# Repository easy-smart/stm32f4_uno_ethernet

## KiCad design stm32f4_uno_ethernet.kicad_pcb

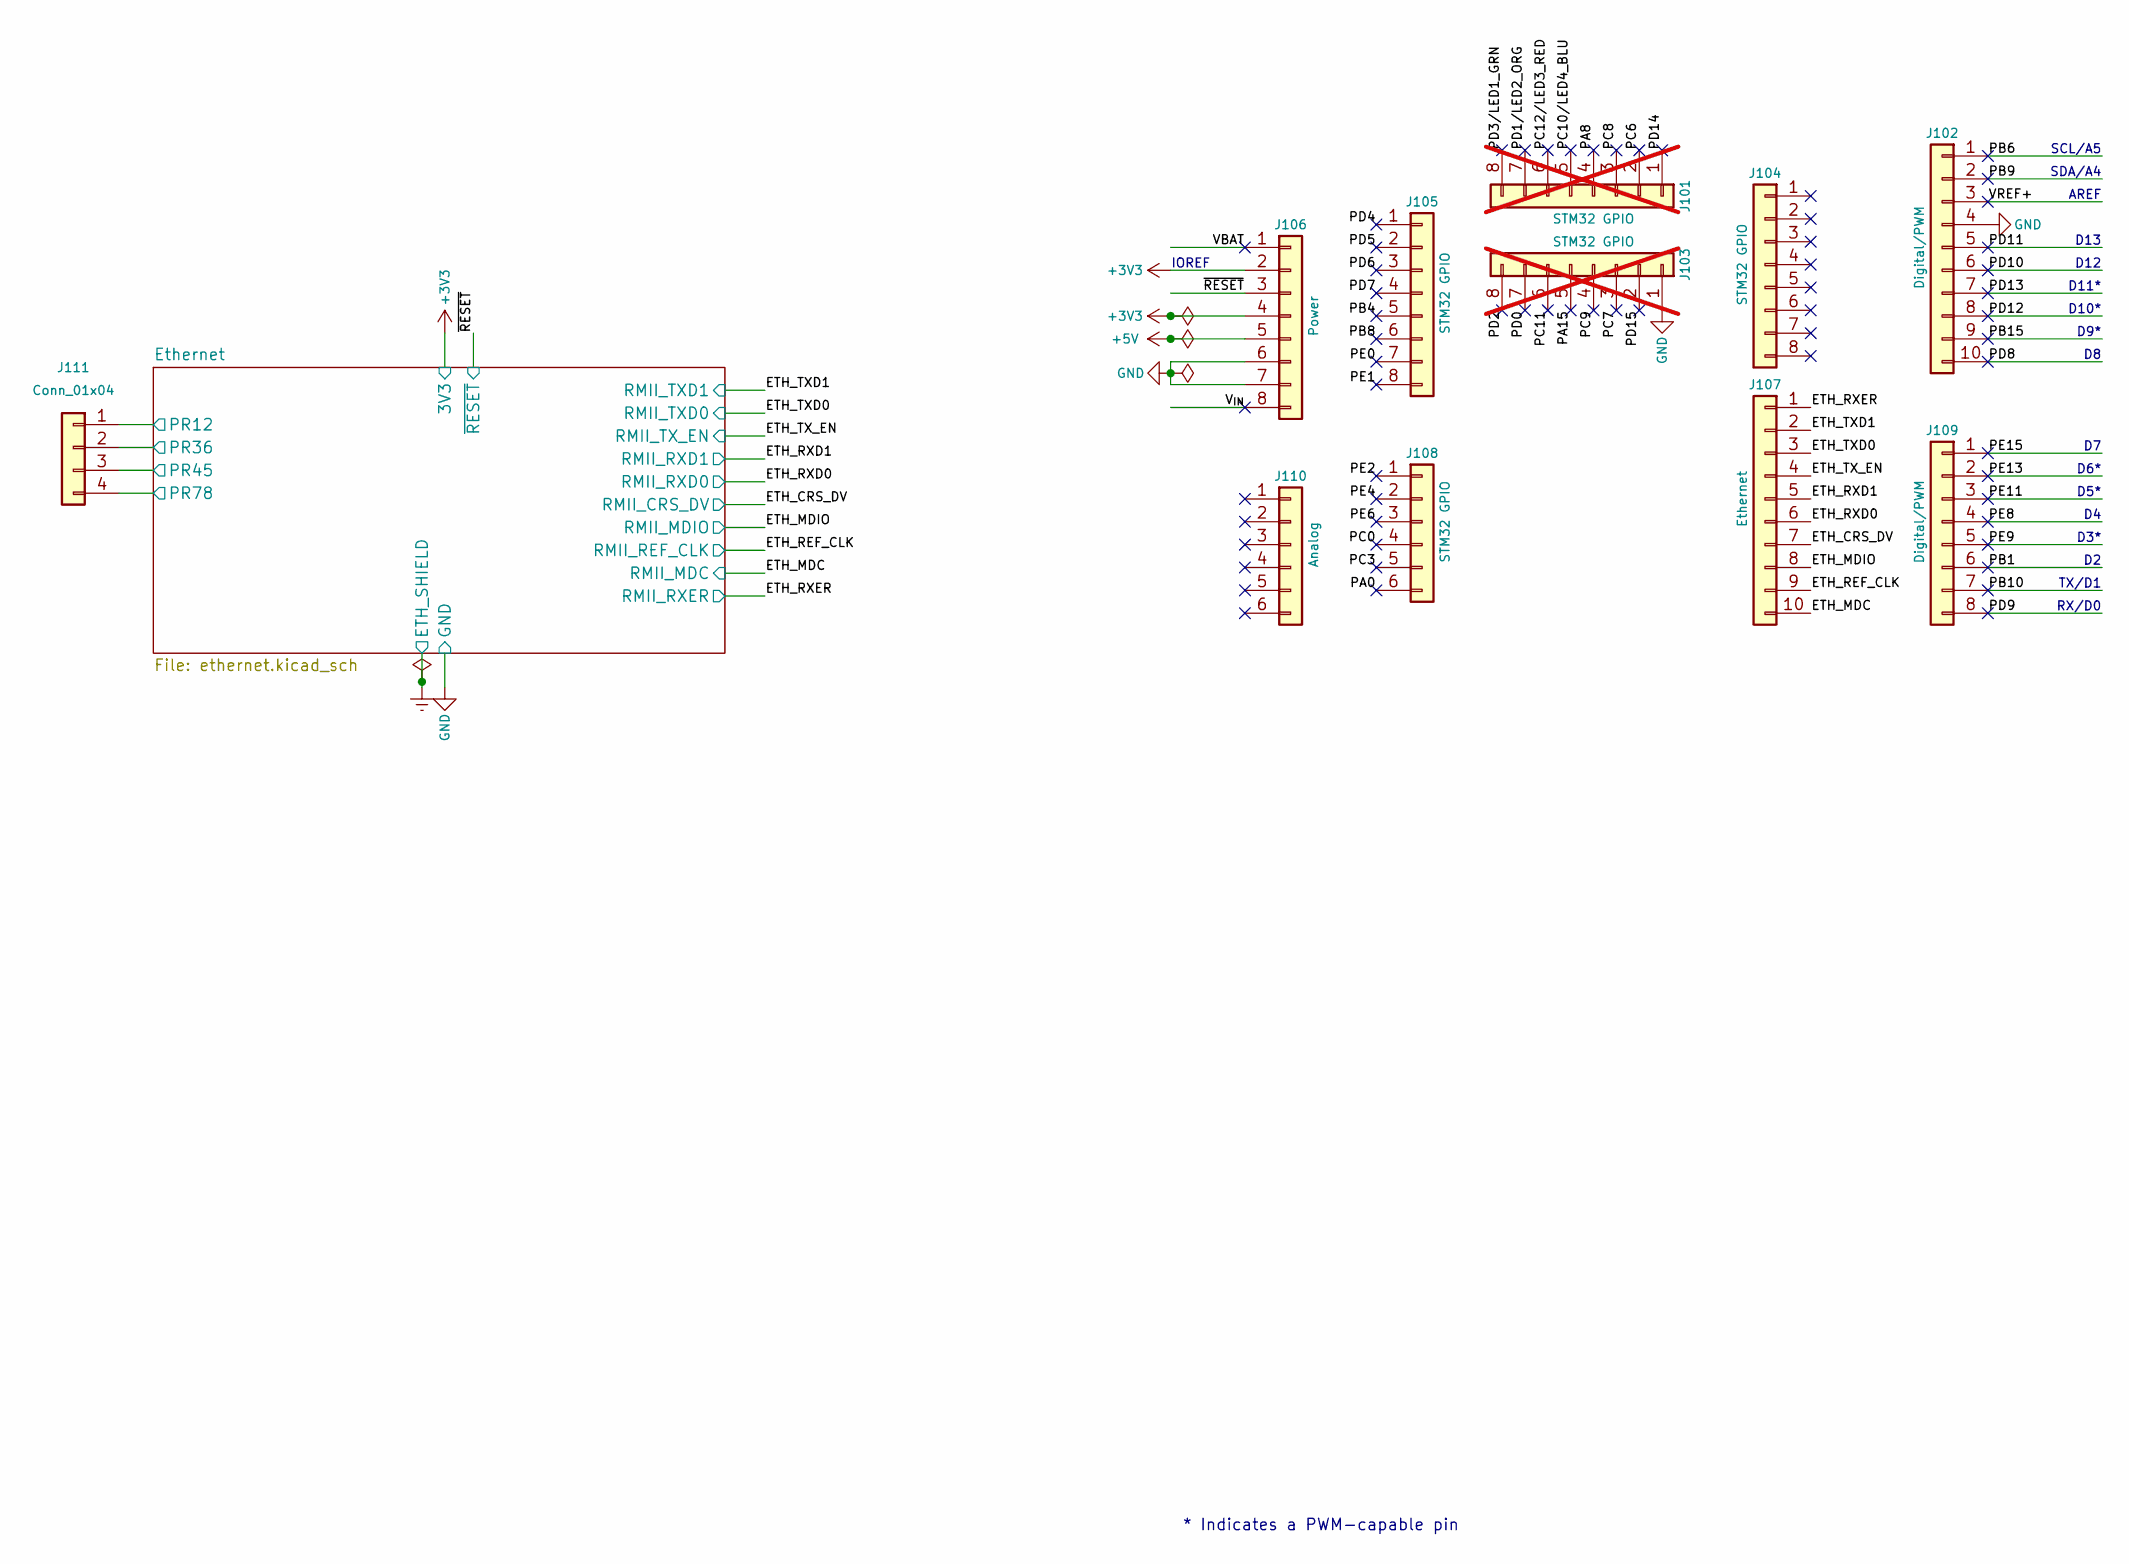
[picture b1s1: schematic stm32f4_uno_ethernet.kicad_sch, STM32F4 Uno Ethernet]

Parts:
J101, J103: STM32 GPIO; PinSocket_1x08_P2.54mm_Vertical; not fitted
J102: Digital/PWM; PinSocket_1x10_P2.54mm_Vertical
J104, J105: STM32 GPIO; PinSocket_1x08_P2.54mm_Vertical
J106: Power; PinSocket_1x08_P2.54mm_Vertical
J107: Ethernet; PinSocket_1x10_P2.54mm_Vertical
J108: STM32 GPIO; PinSocket_1x06_P2.54mm_Vertical
J109: Digital/PWM; PinSocket_1x08_P2.54mm_Vertical
J110: Analog; PinSocket_1x06_P2.54mm_Vertical
J111: Conn_01x04; PinSocket_1x04_P2.54mm_Vertical

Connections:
+3V3: J106.2, J106.4; also elsewhere on the board
+5V: J106.5
/ETH_CRS_DV: J107.7; also elsewhere on the board
/ETH_MDC: J107.10; also elsewhere on the board
/ETH_MDIO: J107.8; also elsewhere on the board
/ETH_REF_CLK: J107.9; also elsewhere on the board
/ETH_RXD0: J107.6; also elsewhere on the board
/ETH_RXD1: J107.5; also elsewhere on the board
/ETH_RXER: J107.1; also elsewhere on the board
/ETH_TXD0: J107.3; also elsewhere on the board
/ETH_TXD1: J107.2; also elsewhere on the board
/ETH_TX_EN: J107.4; also elsewhere on the board
/Ethernet/PR12: J111.1; also elsewhere on the board
/Ethernet/PR36: J111.2; also elsewhere on the board
/Ethernet/PR45: J111.3; also elsewhere on the board
/Ethernet/PR78: J111.4; also elsewhere on the board
/PA0: J108.6
/PB1: J109.6
/PB4: J105.5
/PB6: J102.1
/PB8: J105.6
/PB9: J102.2
/PB10: J109.7
/PB15: J102.9
/PC0: J108.4
/PC3: J108.5
/PD4: J105.1
/PD5: J105.2
/PD6: J105.3
/PD7: J105.4
/PD8: J102.10
/PD9: J109.8
/PD10: J102.6
/PD11: J102.5
/PD12: J102.8
/PD13: J102.7
/PE0: J105.7
/PE1: J105.8
/PE2: J108.1
/PE4: J108.2
/PE6: J108.3
/PE8: J109.4
/PE9: J109.5
/PE11: J109.3
/PE13: J109.2
/PE15: J109.1
/VBAT: J106.1
/VREF+: J102.3
/V_{IN}: J106.8
/~RESET: J106.3; also elsewhere on the board
GND: J102.4, J103.1, J106.6, J106.7; also elsewhere on the board

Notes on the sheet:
AREF
D13
D10*
SCL/A5
SDA/A4
D9*
* Indicates a PWM-capable pin
TX/D1
D3*
D6*
RX/D0
D11*
IOREF
D5*
D12

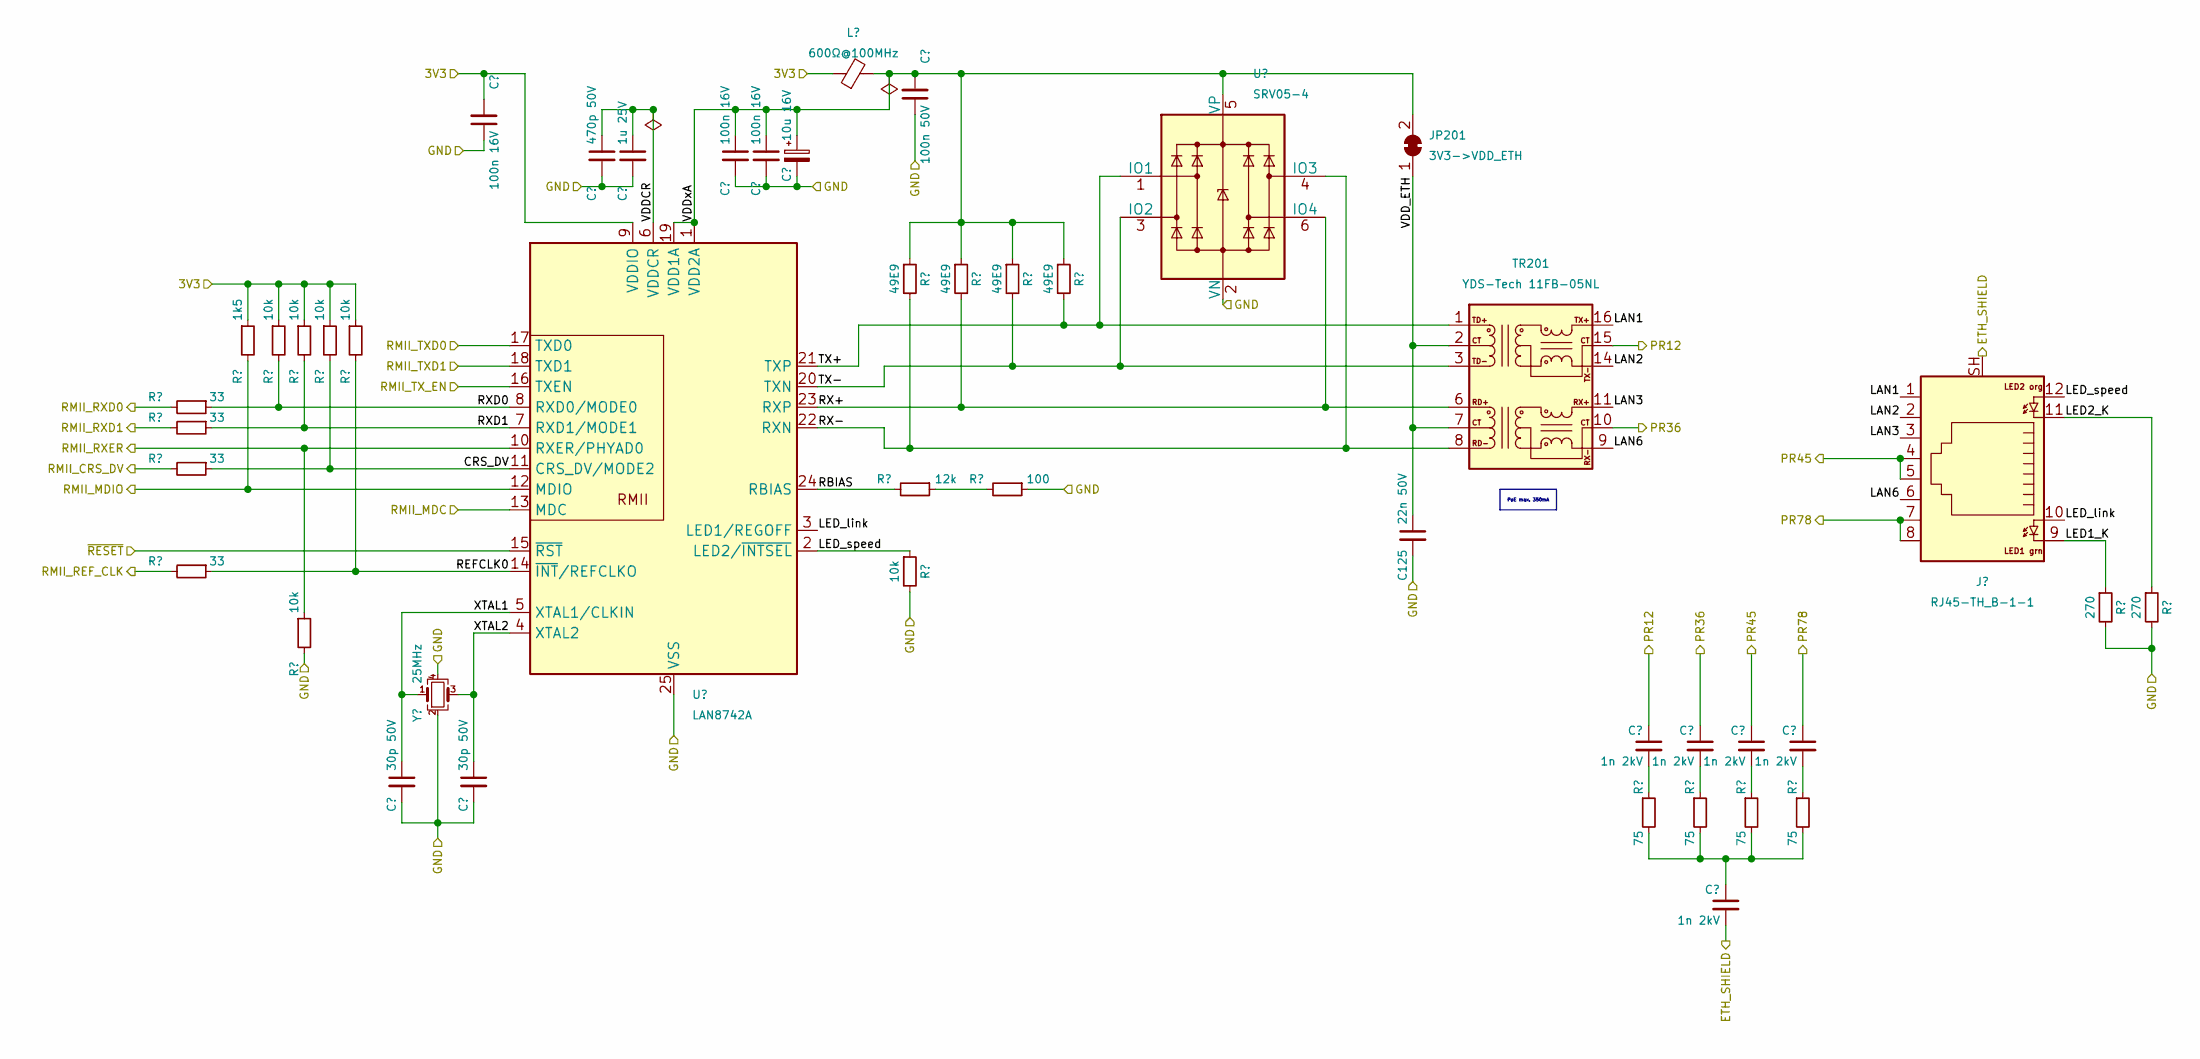
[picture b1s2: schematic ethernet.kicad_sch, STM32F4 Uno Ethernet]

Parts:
C125: 22n 50V; C_0603_1608Metric; Partnumber CL10B223KB8NNNC; JLCPCB Part # C21122
C201: 100n 50V; C_0402_1005Metric; Partnumber CL05B104KB54PNC; JLCPCB Part # C307331
C202, C205, C206: 100n 16V; C_0402_1005Metric; Manufacturer_Part_Number CL05B104KO5NNNC; JLCPCB Part # C1525
C203: 470p 50V; C_0402_1005Metric; Partnumber 0402B471K500NT; JLCPCB Part # C1537
C204: 1u 25V; C_0402_1005Metric; Partnumber CL05A105KA5NQNC; JLCPCB Part # C52923
C207: 10u 16V; CP_EIA-3216-18_Kemet-A; Partnumber TAJA106K016RNJ; JLCPCB Part # C7171
C209, C210: 30p 50V; C_0603_1608Metric; Partnumber 0603CG300J500NT; JLCPCB Part # C1658
C211, C212, C213, C214, C215: 1n 2kV; C_1206_3216Metric; Partnumber 1206B102K202NT; JLCPCB Part # C9196
J201: RJ45-TH_B-1-1; Boomele RJ45-TH_B-1-1; Partnumber RJ45-B-1*1; JLCPCB Part # C138392
JP201: 3V3->VDD_ETH; SolderJumper-2_P1.3mm_Bridged_RoundedPad1.0x1.5mm
L201: 600Ω@100MHz; L_0805_2012Metric; Manufacturer_Part_Number GZ2012D601TF; JLCPCB Part # C1017
R201, R202, R203, R204: 49E9; R_0603_1608Metric; Partnumber 0603WAF499JT5E; JLCPCB Part # C23185
R206, R207, R208, R210, R214, R220: 10k; R_0603_1608Metric; Partnumber 0603WAF1002T5E; JLCPCB Part # C25804
R209: 1k5; R_0603_1608Metric; Partnumber 0603WAF1501T5E; JLCPCB Part # C22843
R211, R212, R215, R219: 33; R_0603_1608Metric; Partnumber 0603WAF330JT5E; JLCPCB Part # C23140
R216: 12k; R_0402_1005Metric; Partnumber 0402WGF1202TCE; JLCPCB Part # C25752
R217: 100; R_0402_1005Metric; Partnumber 0402WGF1000TCE; JLCPCB Part # C25076
R222, R223: 270; R_0603_1608Metric; Partnumber 0603WAF2700T5E; JLCPCB Part # C22966
R224, R225, R226, R227: 75; R_0603_1608Metric; Partnumber 0603WAF750JT5E; JLCPCB Part # C4275
TR201: YDS-Tech 11FB-05NL; Partnumber VP6019 HF; JLCPCB Part # C4154986
U201: SRV05-4; SOT-23-6; Partnumber SRV05-4-P-T7; JLCPCB Part # C85364
U202: LAN8742A; LAN8742AI-CZ-TR; Partnumber LAN8742AI-CZ-TR; JLCPCB Part # C621425
Y201: 25MHz; Crystal_SMD_3225-4Pin_3.2x2.5mm; Partnumber X322525MOB4SI; JLCPCB Part # C9006

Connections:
+3V3: C202.2, L201.1, R206.1, R207.1, R208.1, R209.1, R210.1, U202.9 (VDDIO); also elsewhere on the board
/ETH_CRS_DV: R215.2; also elsewhere on the board
/ETH_MDC: U202.13 (MDC); also elsewhere on the board
/ETH_MDIO: R209.2, U202.12 (MDIO); also elsewhere on the board
/ETH_REF_CLK: R219.2; also elsewhere on the board
/ETH_RXD0: R211.2; also elsewhere on the board
/ETH_RXD1: R212.2; also elsewhere on the board
/ETH_RXER: R214.1, U202.10 (RXER/PHYAD0); also elsewhere on the board
/ETH_TXD0: U202.17 (TXD0); also elsewhere on the board
/ETH_TXD1: U202.18 (TXD1); also elsewhere on the board
/ETH_TX_EN: U202.16 (TXEN); also elsewhere on the board
/Ethernet/CRS_DV: R208.2, R215.1, U202.11 (CRS_DV/MODE2)
/Ethernet/LAN1: J201.1, TR201.16 (TD-)
/Ethernet/LAN2: J201.2, TR201.14 (TD+)
/Ethernet/LAN3: J201.3, TR201.11 (RD-)
/Ethernet/LAN6: J201.6, TR201.9 (RD+)
/Ethernet/LED1_K: J201.9, R222.1
/Ethernet/LED2_K: J201.11, R223.1
/Ethernet/LED_link: J201.10, U202.3 (LED1/REGOFF)
/Ethernet/LED_speed: J201.12, R220.1, U202.2 (LED2/~INTSEL)
/Ethernet/PR12: C211.1, TR201.15 (C_TD); also elsewhere on the board
/Ethernet/PR36: C212.1, TR201.10 (C_RD); also elsewhere on the board
/Ethernet/PR45: C213.1, J201.4, J201.5; also elsewhere on the board
/Ethernet/PR78: C214.1, J201.7, J201.8; also elsewhere on the board
/Ethernet/RBIAS: R216.2, U202.24 (RBIAS)
/Ethernet/REFCLK0: R210.2, R219.1, U202.14 (~INT/REFCLKO)
/Ethernet/RX+: R202.2, TR201.6 (RX-), U201.6 (IO4), U202.23 (RXP)
/Ethernet/RX-: R201.2, TR201.8 (RX+), U201.4 (IO3), U202.22 (RXN)
/Ethernet/RXD0: R206.2, R211.1, U202.8 (RXD0/MODE0)
/Ethernet/RXD1: R207.2, R212.1, U202.7 (RXD1/MODE1)
/Ethernet/TX+: R204.2, TR201.1 (TX-), U201.1 (IO1), U202.21 (TXP)
/Ethernet/TX-: R203.2, TR201.3 (TX+), U201.3 (IO2), U202.20 (TXN)
/Ethernet/VDDCR: C203.1, C204.1, U202.6 (VDDCR)
/Ethernet/VDD_ETH: JP201.1 (A), TR201.2 (C_TX), TR201.7 (C_RX); also elsewhere on the board
/Ethernet/VDDxA: C201.2, C205.1, C206.1, C207.1, JP201.2 (B), L201.2, R201.1, R202.1, R203.1, R204.1, U201.5 (VP), U202.1 (VDD2A), U202.19 (VDD1A)
/Ethernet/XTAL1: C209.1, U202.5 (XTAL1/CLKIN), Y201.1
/Ethernet/XTAL2: C210.1, U202.4 (XTAL2), Y201.3
/~RESET: U202.15 (~RST); also elsewhere on the board
Earth: C215.2, J201.SH
GND: C201.1, C202.1, C203.2, C204.2, C205.2, C206.2, C207.2, C209.2, C210.2, R214.2, R217.1, R220.2, R222.2, R223.2, U201.2 (VN), U202.25 (VSS), Y201.2, Y201.4; also elsewhere on the board
unnamed: C211.2, R224.1
unnamed: C212.2, R225.1
unnamed: C213.2, R226.1
unnamed: C214.2, R227.1
unnamed: C215.1, R224.2, R225.2, R226.2, R227.2
unnamed: R216.1, R217.2

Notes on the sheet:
PoE max. 350mA

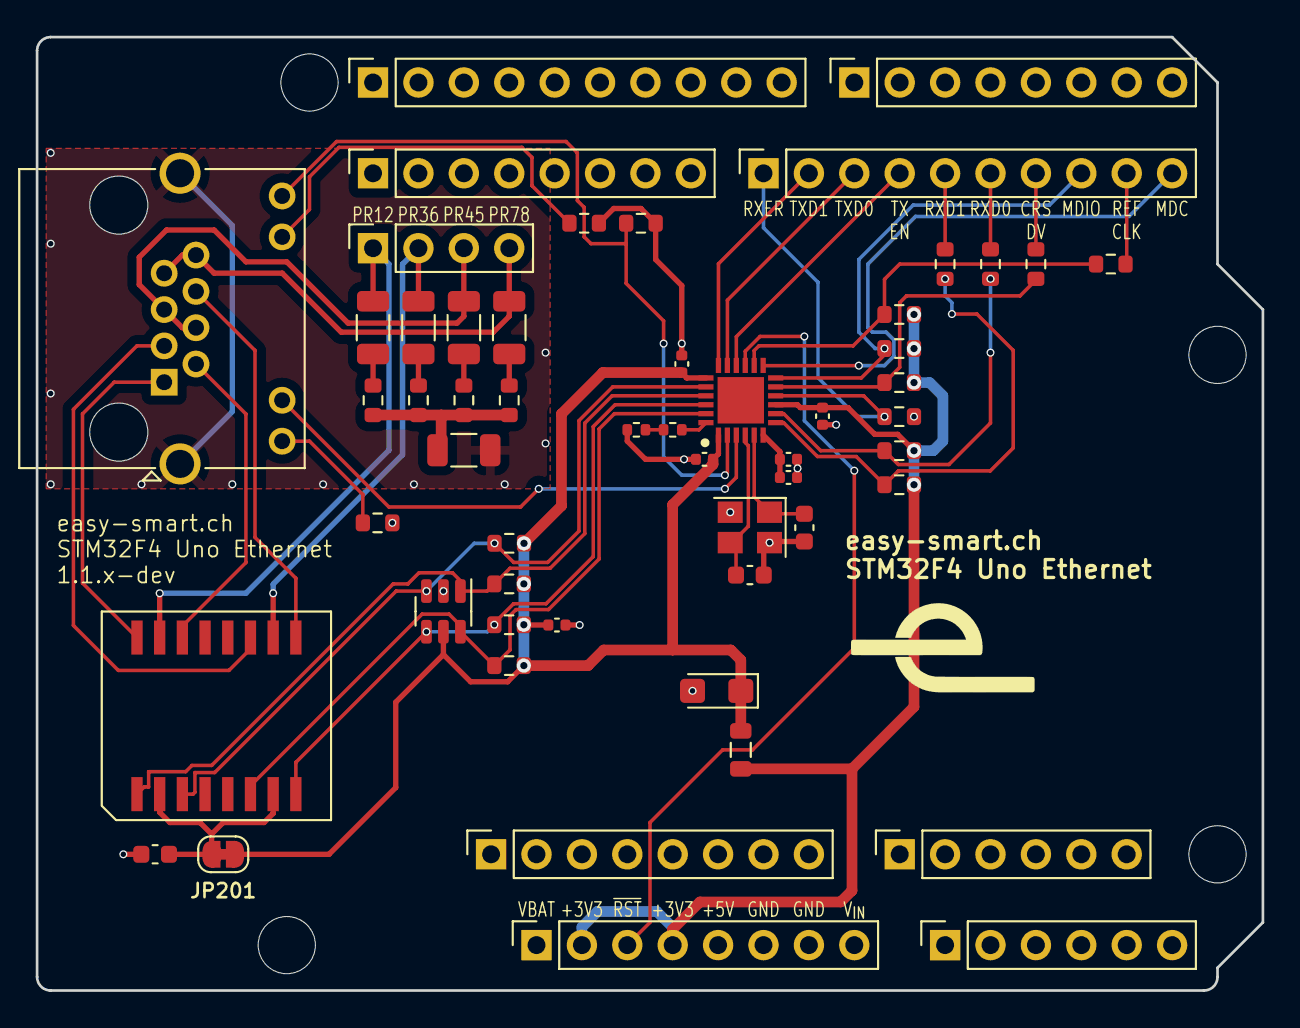
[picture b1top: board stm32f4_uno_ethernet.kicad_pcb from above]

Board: 2 copper layers, 68.6 x 53.3 mm, 58 parts (0 on the bottom side), 46 nets.

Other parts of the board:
C217: 22n 50V; C_0603_1608Metric
MH1, MH2, MH3, MH4: MountingHole_3.2mm

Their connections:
/Ethernet/VDD_ETH: C217.1; also elsewhere on the board
GND: C217.2; also elsewhere on the board

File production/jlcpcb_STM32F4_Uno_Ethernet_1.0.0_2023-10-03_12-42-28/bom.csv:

Designator,Footprint,Quantity,Value,LCSC Part #
C201,0402,1,100n 50V,C307331
"C202, C205, C206",0402,3,100n 16V,C1525
C203,0402,1,470p 50V,C1537
C204,0402,1,1u 25V,C52923
C207,CP_EIA-3216-18_Kemet-A,1,10u 16V,C7171
"C209, C210",0603,2,30p 50V,C1658
"C211, C212, C213, C214, C215",1206,5,1n 2kV,C9196
C217,0603,1,22n 50V,C21122
J201,Boomele RJ45-TH_B-1-1,1,RJ45-TH_B-1-1,C138392
L201,0805,1,600Ω@100MHz,C1017
"R201, R202, R203, R204",0603,4,49E9,C23185
"R206, R207, R208, R210, R214, R220",0603,6,10k,C25804
R209,0603,1,1k5,C22843
"R211, R212, R215, R219",0603,4,33,C23140
R216,0402,1,12k,C25752
R217,0402,1,100,C25076
"R222, R223",0603,2,270,C22966
"R224, R225, R226, R227",0603,4,75,C4275
TR201,YDS-Tech 11FB-05NL,1,YDS-Tech 11FB-05NL,C97692
U201,SOT-23-6,1,SRV05-4,C85364
U202,VQFN-24-1EP_4x4mm_P0.5mm_EP2.45x2.45mm_ThermalVias,1,LAN8742A,C621425
Y201,Crystal_SMD_3225-4Pin_3.2x2.5mm,1,25MHz,C9006

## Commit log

2023-09-11 PCB finished
2023-09-12 Replace transformer, replace RJ45 3D model
2023-09-12 Change LAN footprint
2023-09-14 Add ETH_RXER
2023-09-14 Set DNP
2023-09-20 #1 Use new central library KiCad-Lib
2023-09-20 Add PCD 3D model
2023-09-24 Move PoE pin socket and add earth zone
2023-10-02 #2 Add silkscreen texts
2023-10-02 #3 Match pcb to poe and base
2023-10-03 Release 1.0.0 sent to JLCPCB
2023-10-03 PCB production confirmed
2023-10-14 Add product photos
2023-10-14 #4 Wrong polarity on C207
2023-10-17 Add workflow
2024-11-28 #8 Add all pin sockets on ethernet
2024-11-28 #7 Change ethernet signal transformer
